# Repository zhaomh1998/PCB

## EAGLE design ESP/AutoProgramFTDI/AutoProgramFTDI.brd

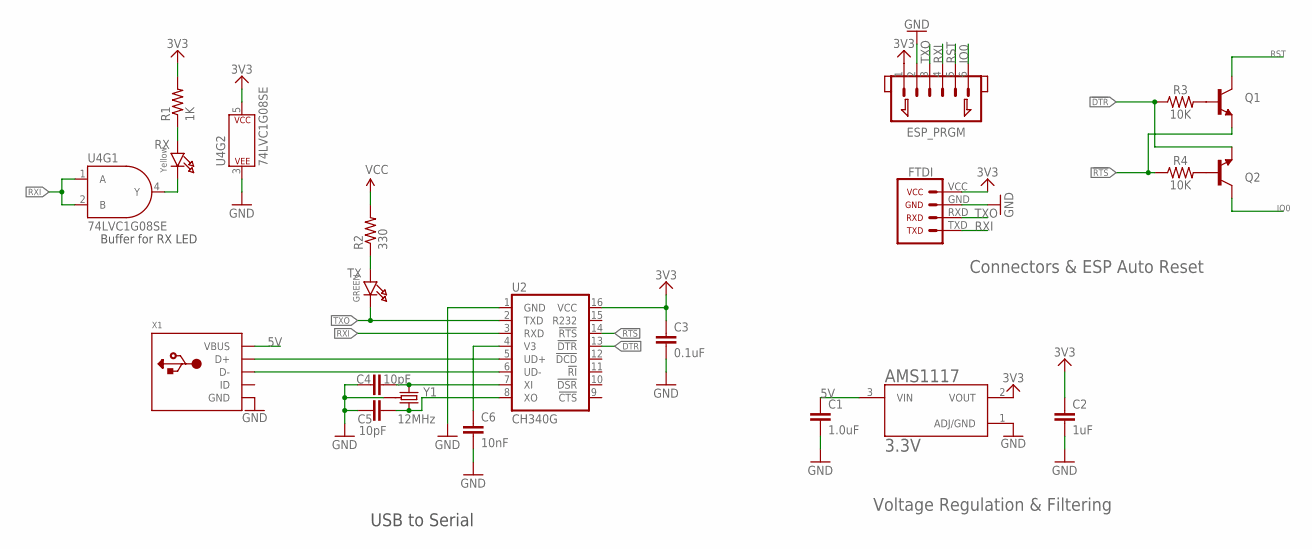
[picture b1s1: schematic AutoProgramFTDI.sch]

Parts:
AMS1117: 3.3V; SOT229P700X180-4N
C1: 1.0uF; 0603-CAP
C2: 1uF; 0603-CAP
C3: 0.1uF; 0603-CAP
C4, C5: 10pF; 0603-CAP
C6: 10nF; 0603-CAP
ESP_PRGM: JST_1.25_6P; JST1.25_6P
Q1, Q2: TRANSISTOR_NPNSOT23-3; SPARKFUN_SOT23-3
R1: 1K; 0603
R2: 330; 0603
R3, R4: 10K; 0603
RX: Yellow; MICROBUILDER_CHIPLED_0603
TX: GREEN; MICROBUILDER_CHIPLED_0603
U2: CH340G; SO016
U4: 74LVC1G08SE; SOT353
U$6: FTDI; 1X06
X1: USB_MICRO_20329_V2; MICROUSB_4UCONN_20329_V2
Y1: 12MHz; CRYSTAL-SMD-3.2X2.5

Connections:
3.3V: AMS1117.2 (VOUT), C2.1, C3.1, ESP_PRGM.1, R1.2, U2.16 (VCC), U4.5 (P$V+), U$6.VCC
5V: AMS1117.3 (VIN), C1.1, X1.VBUS
!DTR: Q2.2 (E), R3.1, U2.13 (!DTR)
!RTS: Q1.2 (E), R4.1, U2.14 (!RTS)
GND: AMS1117.1 (ADJ/GND), C1.2, C2.2, C3.2, C4.1, C5.1, C6.2, ESP_PRGM.2, U2.1 (GND), U4.3 (P$V-), U$6.GND, X1.BASE@1 (GND), X1.BASE@2 (GND), X1.GND, X1.SPRT@1 (GND), X1.SPRT@2 (GND), X1.SPRT@3 (GND), X1.SPRT@4 (GND), Y1.2 (GND), Y1.4 (GND)
IO0: ESP_PRGM.6, Q2.3 (C)
unnamed: R2.1, TX.A
unnamed: R1.1, RX.A
unnamed: C5.2, U2.8 (XO), Y1.3 (2)
unnamed: C4.2, U2.7 (XI), Y1.1
unnamed: RX.C, U4.4 (Y)
unnamed: U2.6 (UD-), X1.D-
unnamed: U2.5 (UD+), X1.D+
unnamed: Q1.1 (B), R3.2
unnamed: Q2.1 (B), R4.2
RST: ESP_PRGM.5, Q1.3 (C)
RXI: ESP_PRGM.4, U2.3 (RXD), U4.1 (A), U4.2 (B), U$6.TXD
TXO: ESP_PRGM.3, TX.C, U2.2 (TXD), U$6.RXD
V3: C6.1, U2.4 (V3)
VCC: R2.2

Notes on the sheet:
USB to Serial
Buffer for RX LED
Voltage Regulation & Filtering
Connectors & ESP Auto Reset

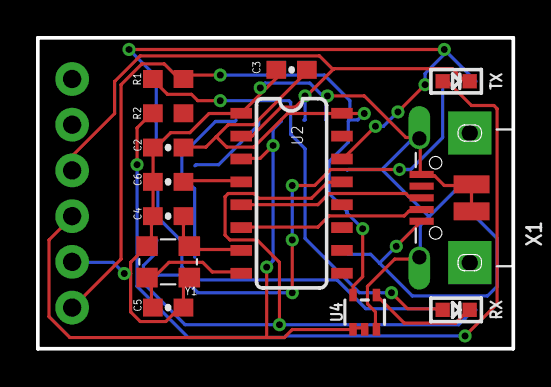
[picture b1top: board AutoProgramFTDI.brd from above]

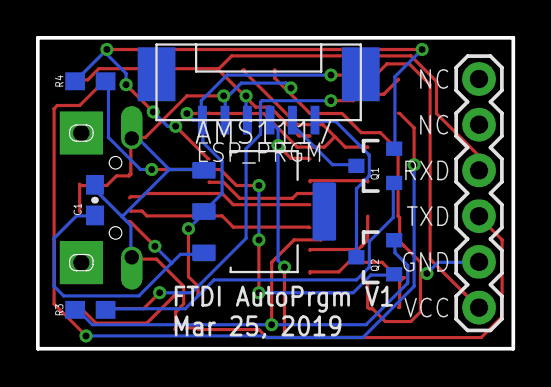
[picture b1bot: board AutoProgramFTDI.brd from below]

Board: 2 copper layers, 26.4 x 17.3 mm, 21 parts (8 on the bottom side), 19 nets.

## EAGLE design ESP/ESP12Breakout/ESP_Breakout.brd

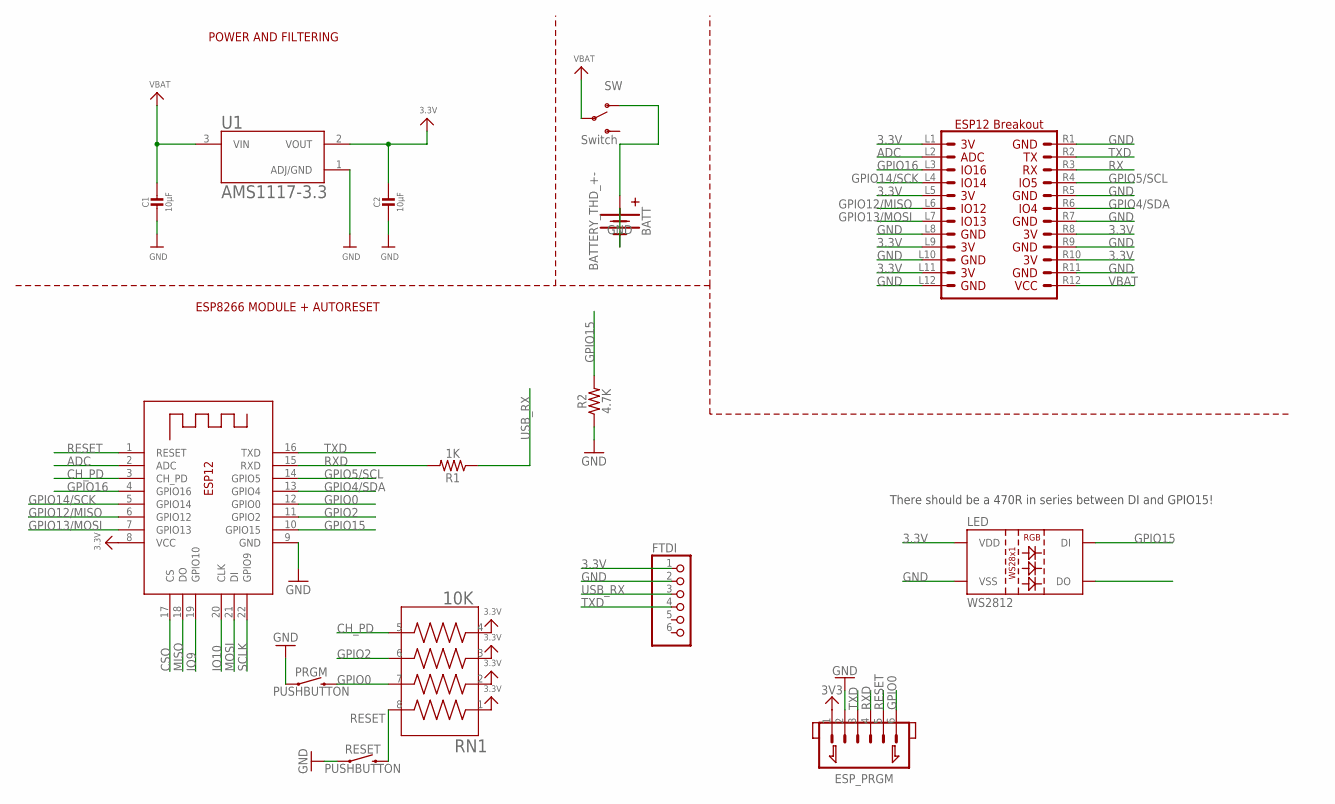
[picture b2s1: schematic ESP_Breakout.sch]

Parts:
BATT: BATTERY_THD_+-; 1X02_PLUS_MINUS
C1, C2: 10µF; CAP_0603
ESP_PRGM: JST_1.25_6P; JST1.25_6P
FTDI: PINHD-1X6; 1X06
LED: WS2812; LED-TRICOLOR-5050-IC
PRGM: PUSHBUTTON; TACTILE_SWITCH_SMD_6.0X3.5MM
R1: 1K; 0603
R2: 4.7K; 0603
RESET: PUSHBUTTON; TACTILE_SWITCH_SMD_6.0X3.5MM
RN1: 10K; RESCAF80P320X160X60-8N
SW: Switch; SWITCH_SPDT_PTH_11.6X4.0MM
U1: AMS1117-3.3; SOT229P700X180-4N
U$7: ESP12_BREAKOUT; ESP12_BREAKOUT_CONN
X2: ESP-12; ESP-12E

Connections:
3.3V: C2.1, ESP_PRGM.1, FTDI.1, LED.VDD, RN1.1, RN1.2, RN1.3, RN1.4, U1.2 (VOUT), U$7.L1, U$7.L5, U$7.L9, U$7.L11, U$7.R8, U$7.R10, X2.8 (VCC)
ADC: U$7.L2, X2.2 (ADC)
CH_PD: RN1.5, X2.3 (CH_PD)
CSO: X2.17 (CS)
GND: BATT.-, C1.2, C2.2, ESP_PRGM.2, FTDI.2, LED.VSS, PRGM.1, R2.1, RESET.1, U1.1 (ADJ/GND), U$7.L8, U$7.L10, U$7.L12, U$7.R1, U$7.R5, U$7.R7, U$7.R9, U$7.R11, X2.9 (GND)
GPIO0: ESP_PRGM.6, PRGM.2, RN1.7, X2.12 (GPIO0)
GPIO2: RN1.6, X2.11 (GPIO2)
GPIO4/SDA: U$7.R6, X2.13 (GPIO4)
GPIO5/SCL: U$7.R4, X2.14 (GPIO5)
GPIO12/MISO: U$7.L6, X2.6 (GPIO12)
GPIO13/MOSI: U$7.L7, X2.7 (GPIO13)
GPIO14/SCK: U$7.L4, X2.5 (GPIO14)
GPIO15: LED.DIN (DI), R2.2, X2.10 (GPIO15)
GPIO16: U$7.L3, X2.4 (GPIO16)
IO9: X2.19 (GPIO10)
IO10: X2.20 (CLK)
MISO: X2.18 (DO)
MOSI: X2.21 (DI)
unnamed: BATT.+, SW.1 (O)
RESET: ESP_PRGM.5, RESET.2, RN1.8, X2.1 (RESET)
RX: U$7.R3
RXD: ESP_PRGM.4, R1.2, X2.15 (RXD)
SCLK: X2.22 (GPIO9)
TXD: ESP_PRGM.3, FTDI.4, U$7.R2, X2.16 (TXD)
USB_RX: FTDI.3, R1.1
VBAT: C1.1, SW.2, U1.3 (VIN), U$7.R12

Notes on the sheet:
POWER AND FILTERING
ESP8266 MODULE + AUTORESET
There should be a 470R in series between DI and GPIO15!

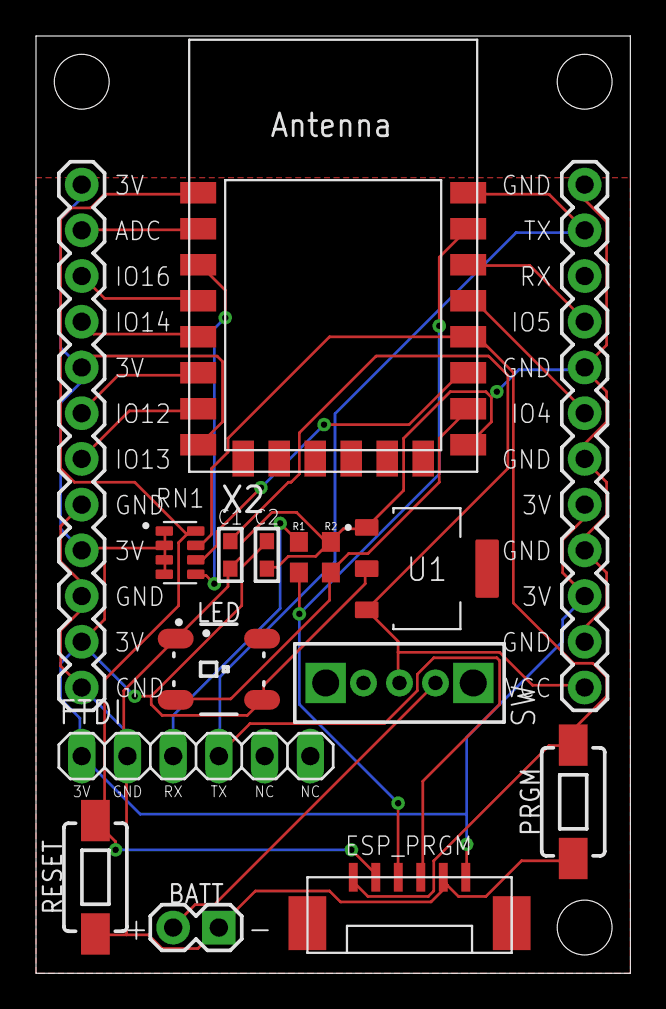
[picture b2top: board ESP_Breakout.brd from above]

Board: 2 copper layers, 33.0 x 52.1 mm, 15 parts (0 on the bottom side), 19 nets.

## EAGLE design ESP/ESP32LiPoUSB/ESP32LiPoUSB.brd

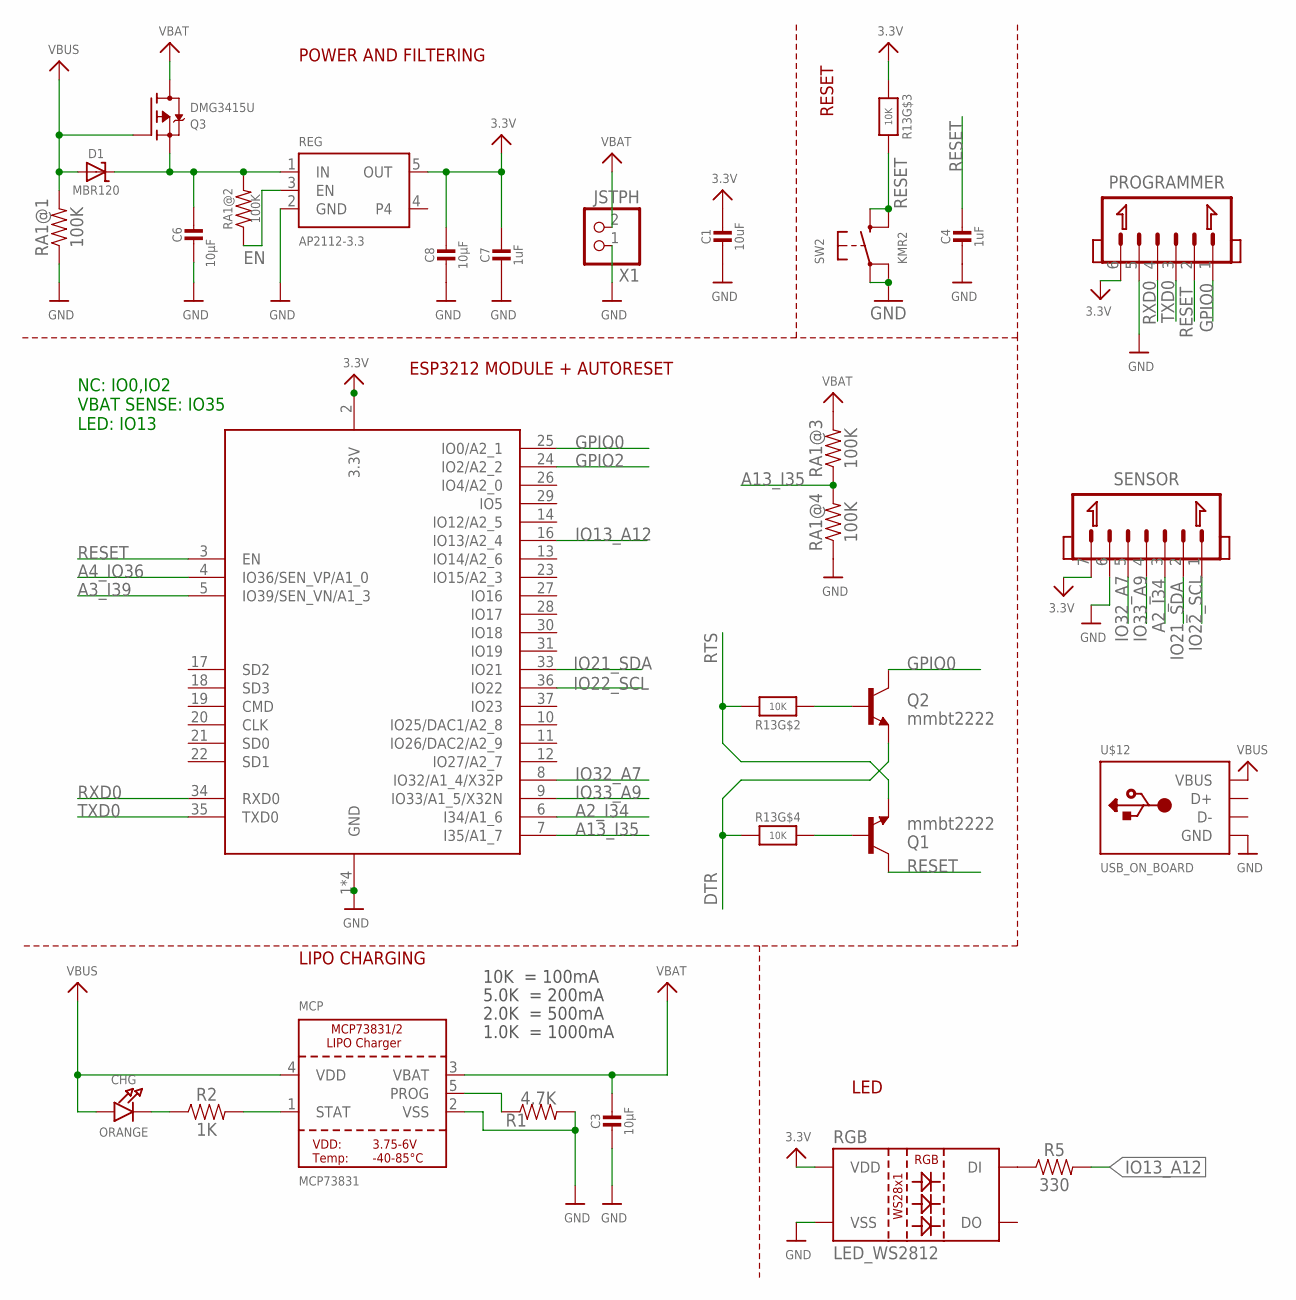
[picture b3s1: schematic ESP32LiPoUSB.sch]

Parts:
C1: 10uF; CAP_0805
C3, C8: 10µF; CAP_0805
C4, C7: 1uF; CAP_0603
C6: 10µF; CAP_0603
CHG: ORANGE; MICROBUILDER_CHIPLED_0603
D1: MBR120; SOD-123
MCP: MCP73831; SOT23-5
PROGRAMMER: JST_1.25_6P; JST1.25_6P
Q1, Q2: mmbt2222; SOT23-3
Q3: DMG3415U; SOT23-R
R1: 4.7K; 0603
R2: 1K; 0603
R5: 330; 0603
R13: 10K; RESPACK_4X0603
RA1: 100K; RESCAF80P320X160X60-8N
REG: AP2112-3.3; SOT23-5
RGB: LED_WS2812; LED-TRICOLOR-5050-IC
SENSOR: JST_1.25_7P; JST1.25_7P
SW2: KMR2; BTN_KMR2_4.6X2.8
U$12: USB_ON_BOARD
X1: JSTPH; JSTPH2
X2: ESP32_WROOM32_SKINNY; WROOM32_SKINNY

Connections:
3.3V: C1.1, C7.1, C8.1, PROGRAMMER.6, R13.3 (1), REG.5 (OUT), RGB.VDD, SENSOR.7, X2.2 (3.3V)
A2_I34: SENSOR.3, X2.6 (I34/A1_6)
A3_I39: X2.5 (IO39/SEN_VN/A1_3)
A4_IO36: X2.4 (IO36/SEN_VP/A1_0)
A13_I35: RA1.3 (1), RA1.8 (2), X2.7 (I35/A1_7)
DTR: Q2.2 (E), R13.4 (1)
EN: RA1.2 (1), REG.3 (EN)
GND: C1.2, C3.2, C4.2, C6.2, C7.2, C8.2, MCP.2 (VSS), PROGRAMMER.5, R1.2, RA1.1, RA1.4 (1), REG.2 (GND), RGB.VSS, SENSOR.6, SW2.A, SW2.A' (P1), U$12.GND, X1.1, X2.1 (GND), X2.15 (GND), X2.38 (GND), X2.P$1 (GND)
GPIO0: PROGRAMMER.1, Q2.3 (C), X2.25 (IO0/A2_1)
GPIO2: X2.24 (IO2/A2_2)
IO13_A12: R5.2, X2.16 (IO13/A2_4)
IO21_SDA: SENSOR.2, X2.33 (IO21)
IO22_SCL: SENSOR.1, X2.36 (IO22)
IO32_A7: SENSOR.5, X2.8 (IO32/A1_4/X32P)
IO33_A9: SENSOR.4, X2.9 (IO33/A1_5/X32N)
unnamed: CHG.C, R2.1
unnamed: R5.1, RGB.DIN (DI)
unnamed: MCP.1 (STAT), R2.2
unnamed: MCP.5 (PROG), R1.1
unnamed: C6.1, D1.C, Q3.2 (S), RA1.6 (2), REG.1 (IN)
unnamed: Q1.1 (B), R13.5 (2)
unnamed: Q2.1 (B), R13.2 (1)
RESET: C4.1, PROGRAMMER.2, Q1.3 (C), R13.6 (2), SW2.B (S), SW2.B' (S1), X2.3 (EN)
RTS: Q1.2 (E), R13.7 (2)
RXD0: PROGRAMMER.4, X2.34 (RXD0)
TXD0: PROGRAMMER.3, X2.35 (TXD0)
VBAT: C3.1, MCP.3 (VBAT), Q3.3 (D), RA1.7 (2), X1.2
VBUS: CHG.A, D1.A, MCP.4 (VDD), Q3.1 (G), RA1.5 (2), U$12.VCC (VBUS)

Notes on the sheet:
POWER AND FILTERING
RESET
10K = 100mA
5.0K = 200mA
2.0K = 500mA
1.0K = 1000mA
LIPO CHARGING
LED
ESP3212 MODULE + AUTORESET
NC: IO0,IO2 VBAT SENSE: IO35 LED: IO13

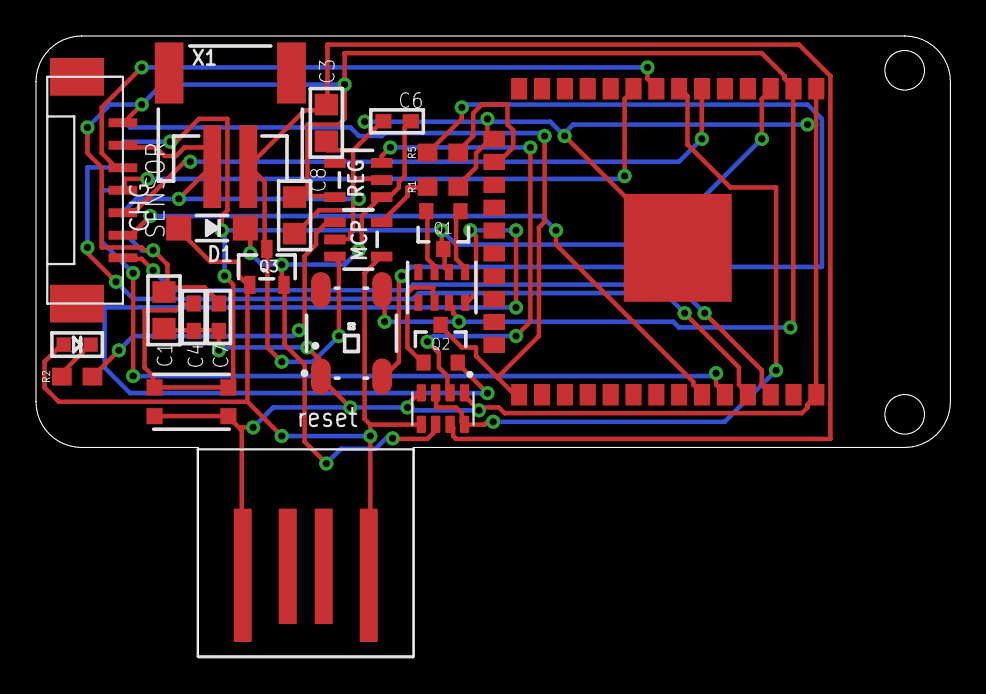
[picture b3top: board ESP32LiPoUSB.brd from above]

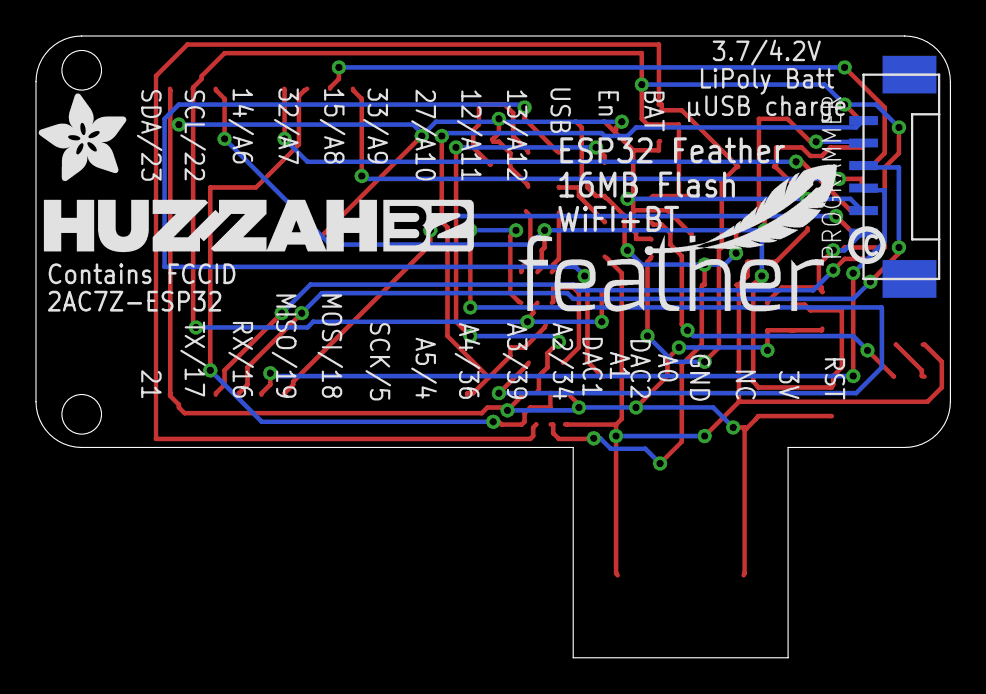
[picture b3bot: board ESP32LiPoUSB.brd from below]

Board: 2 copper layers, 50.8 x 34.5 mm, 29 parts (5 on the bottom side), 25 nets.

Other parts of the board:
U$7: ADAFRUIT_5MM
U$9: FEATHERLOGO_MED
U$13: PCBFEAT-REV-040
U$43: HUZZAH32

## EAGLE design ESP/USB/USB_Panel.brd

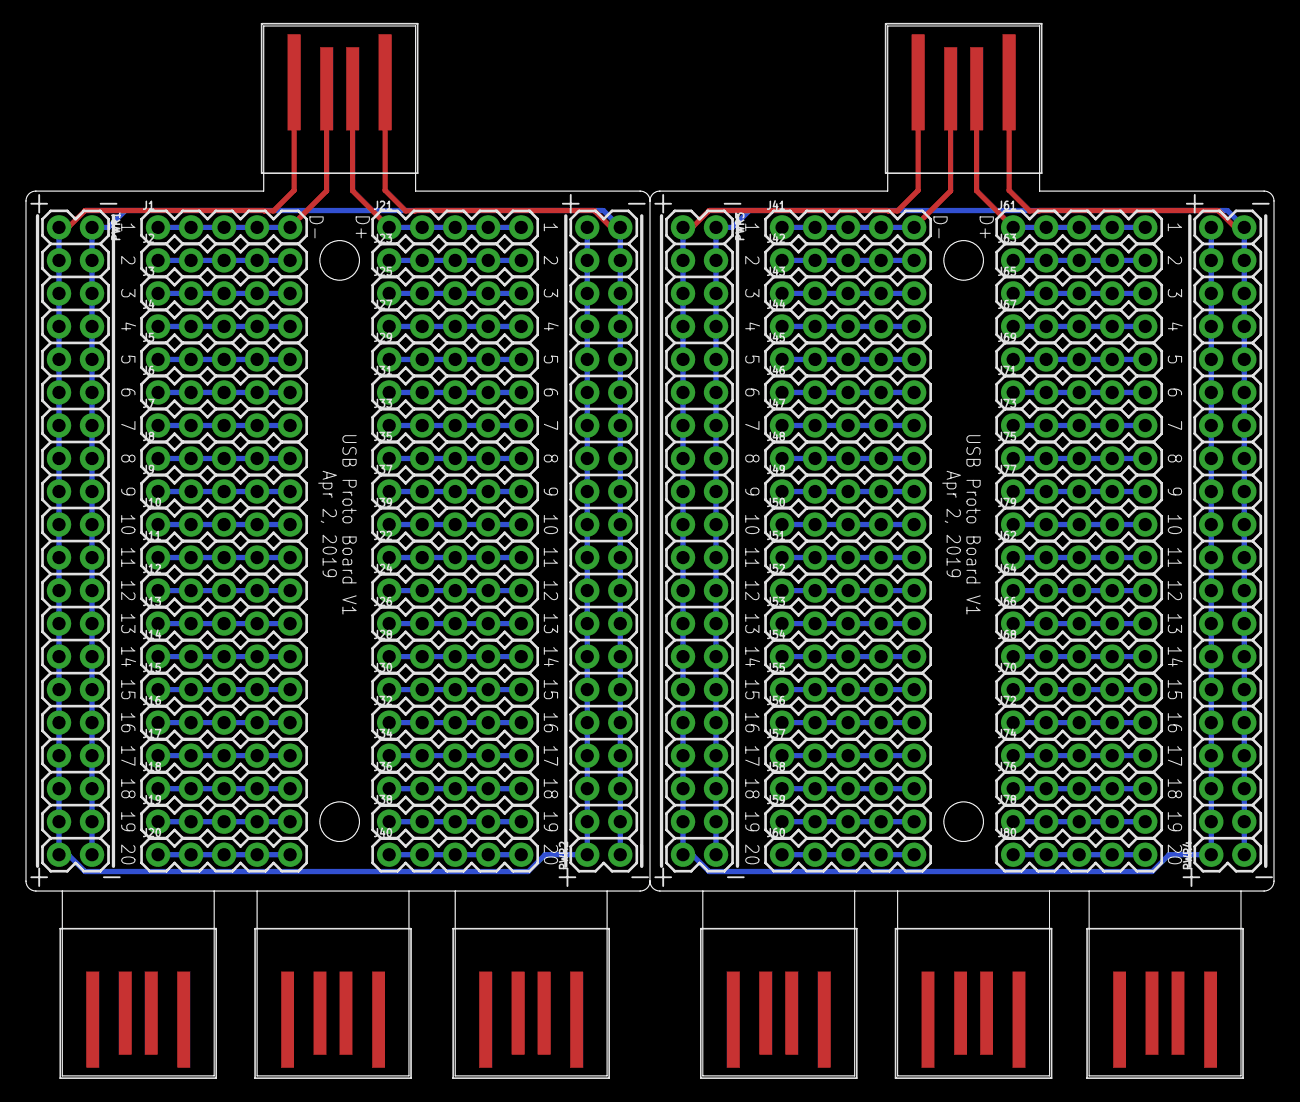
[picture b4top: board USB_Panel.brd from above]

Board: 2 copper layers, 96.0 x 66.5 mm, 92 parts (0 on the bottom side), 84 nets.

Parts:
J1, J2, J3, J4, J5, J6, J7, J8, J9, J10, J11, J12, J13, J14, J15, J16, J17, J18, J19, J20, J21, J22, J23, J24, J25, J26, J27, J28, J29, J30, J31, J32, J33, J34, J35, J36, J37, J38, J39, J40, J41, J42, J43, J44, J45, J46, J47, J48, J49, J50, J51, J52, J53, J54, J55, J56, J57, J58, J59, J60, J61, J62, J63, J64, J65, J66, J67, J68, J69, J70, J71, J72, J73, J74, J75, J76, J77, J78, J79, J80: 1X05
PWR1, PWR2, PWR3, PWR4: CONN_20X2; 2X20
U$1, U$2, U$3, U$4, U$5, U$6, U$7, U$8: USB_ON_BOARD

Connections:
unnamed: J1.1, J1.2, J1.3, J1.4, J1.5, U$2.D-
unnamed: J2.1, J2.2, J2.3, J2.4, J2.5
unnamed: J3.1, J3.2, J3.3, J3.4, J3.5
unnamed: J4.1, J4.2, J4.3, J4.4, J4.5
unnamed: J5.1, J5.2, J5.3, J5.4, J5.5
unnamed: J6.1, J6.2, J6.3, J6.4, J6.5
unnamed: J7.1, J7.2, J7.3, J7.4, J7.5
unnamed: J8.1, J8.2, J8.3, J8.4, J8.5
unnamed: J9.1, J9.2, J9.3, J9.4, J9.5
unnamed: J10.1, J10.2, J10.3, J10.4, J10.5
unnamed: J11.1, J11.2, J11.3, J11.4, J11.5
unnamed: J12.1, J12.2, J12.3, J12.4, J12.5
unnamed: J13.1, J13.2, J13.3, J13.4, J13.5
unnamed: J14.1, J14.2, J14.3, J14.4, J14.5
unnamed: J15.1, J15.2, J15.3, J15.4, J15.5
unnamed: J16.1, J16.2, J16.3, J16.4, J16.5
unnamed: J17.1, J17.2, J17.3, J17.4, J17.5
unnamed: J18.1, J18.2, J18.3, J18.4, J18.5
unnamed: J19.1, J19.2, J19.3, J19.4, J19.5
unnamed: J20.1, J20.2, J20.3, J20.4, J20.5
unnamed: J21.1, J21.2, J21.3, J21.4, J21.5, U$2.D+
unnamed: J22.1, J22.2, J22.3, J22.4, J22.5
unnamed: J23.1, J23.2, J23.3, J23.4, J23.5
unnamed: J24.1, J24.2, J24.3, J24.4, J24.5
unnamed: J25.1, J25.2, J25.3, J25.4, J25.5
unnamed: J26.1, J26.2, J26.3, J26.4, J26.5
unnamed: J27.1, J27.2, J27.3, J27.4, J27.5
unnamed: J28.1, J28.2, J28.3, J28.4, J28.5
unnamed: J29.1, J29.2, J29.3, J29.4, J29.5
unnamed: J30.1, J30.2, J30.3, J30.4, J30.5
unnamed: J31.1, J31.2, J31.3, J31.4, J31.5
unnamed: J32.1, J32.2, J32.3, J32.4, J32.5
unnamed: J33.1, J33.2, J33.3, J33.4, J33.5
unnamed: J34.1, J34.2, J34.3, J34.4, J34.5
unnamed: J35.1, J35.2, J35.3, J35.4, J35.5
unnamed: J36.1, J36.2, J36.3, J36.4, J36.5
unnamed: J37.1, J37.2, J37.3, J37.4, J37.5
unnamed: J38.1, J38.2, J38.3, J38.4, J38.5
unnamed: J39.1, J39.2, J39.3, J39.4, J39.5
unnamed: J40.1, J40.2, J40.3, J40.4, J40.5
unnamed: PWR1.1, PWR1.3, PWR1.5, PWR1.7, PWR1.9, PWR1.11, PWR1.13, PWR1.15, PWR1.17, PWR1.19, PWR1.21, PWR1.23, PWR1.25, PWR1.27, PWR1.29, PWR1.31, PWR1.33, PWR1.35, PWR1.37, PWR1.39, PWR2.2, PWR2.4, PWR2.6, PWR2.8, PWR2.10, PWR2.12, PWR2.14, PWR2.16, PWR2.18, PWR2.20, PWR2.22, PWR2.24, PWR2.26, PWR2.28, PWR2.30, PWR2.32, PWR2.34, PWR2.36, PWR2.38, PWR2.40, U$2.VCC
unnamed: PWR1.2, PWR1.4, PWR1.6, PWR1.8, PWR1.10, PWR1.12, PWR1.14, PWR1.16, PWR1.18, PWR1.20, PWR1.22, PWR1.24, PWR1.26, PWR1.28, PWR1.30, PWR1.32, PWR1.34, PWR1.36, PWR1.38, PWR1.40, PWR2.1, PWR2.3, PWR2.5, PWR2.7, PWR2.9, PWR2.11, PWR2.13, PWR2.15, PWR2.17, PWR2.19, PWR2.21, PWR2.23, PWR2.25, PWR2.27, PWR2.29, PWR2.31, PWR2.33, PWR2.35, PWR2.37, PWR2.39, U$2.GND
unnamed: J41.1, J41.2, J41.3, J41.4, J41.5, U$1.D-
unnamed: J42.1, J42.2, J42.3, J42.4, J42.5
unnamed: J43.1, J43.2, J43.3, J43.4, J43.5
unnamed: J44.1, J44.2, J44.3, J44.4, J44.5
unnamed: J45.1, J45.2, J45.3, J45.4, J45.5
unnamed: J46.1, J46.2, J46.3, J46.4, J46.5
unnamed: J47.1, J47.2, J47.3, J47.4, J47.5
unnamed: J48.1, J48.2, J48.3, J48.4, J48.5
unnamed: J49.1, J49.2, J49.3, J49.4, J49.5
unnamed: J50.1, J50.2, J50.3, J50.4, J50.5
unnamed: J51.1, J51.2, J51.3, J51.4, J51.5
unnamed: J52.1, J52.2, J52.3, J52.4, J52.5
unnamed: J53.1, J53.2, J53.3, J53.4, J53.5
unnamed: J54.1, J54.2, J54.3, J54.4, J54.5
unnamed: J55.1, J55.2, J55.3, J55.4, J55.5
unnamed: J56.1, J56.2, J56.3, J56.4, J56.5
unnamed: J57.1, J57.2, J57.3, J57.4, J57.5
unnamed: J58.1, J58.2, J58.3, J58.4, J58.5
unnamed: J59.1, J59.2, J59.3, J59.4, J59.5
unnamed: J60.1, J60.2, J60.3, J60.4, J60.5
unnamed: J61.1, J61.2, J61.3, J61.4, J61.5, U$1.D+
unnamed: J62.1, J62.2, J62.3, J62.4, J62.5
unnamed: J63.1, J63.2, J63.3, J63.4, J63.5
unnamed: J64.1, J64.2, J64.3, J64.4, J64.5
unnamed: J65.1, J65.2, J65.3, J65.4, J65.5
unnamed: J66.1, J66.2, J66.3, J66.4, J66.5
unnamed: J67.1, J67.2, J67.3, J67.4, J67.5
unnamed: J68.1, J68.2, J68.3, J68.4, J68.5
unnamed: J69.1, J69.2, J69.3, J69.4, J69.5
unnamed: J70.1, J70.2, J70.3, J70.4, J70.5
unnamed: J71.1, J71.2, J71.3, J71.4, J71.5
unnamed: J72.1, J72.2, J72.3, J72.4, J72.5
unnamed: J73.1, J73.2, J73.3, J73.4, J73.5
unnamed: J74.1, J74.2, J74.3, J74.4, J74.5
unnamed: J75.1, J75.2, J75.3, J75.4, J75.5
unnamed: J76.1, J76.2, J76.3, J76.4, J76.5
unnamed: J77.1, J77.2, J77.3, J77.4, J77.5
unnamed: J78.1, J78.2, J78.3, J78.4, J78.5
unnamed: J79.1, J79.2, J79.3, J79.4, J79.5
unnamed: J80.1, J80.2, J80.3, J80.4, J80.5
unnamed: PWR3.1, PWR3.3, PWR3.5, PWR3.7, PWR3.9, PWR3.11, PWR3.13, PWR3.15, PWR3.17, PWR3.19, PWR3.21, PWR3.23, PWR3.25, PWR3.27, PWR3.29, PWR3.31, PWR3.33, PWR3.35, PWR3.37, PWR3.39, PWR4.2, PWR4.4, PWR4.6, PWR4.8, PWR4.10, PWR4.12, PWR4.14, PWR4.16, PWR4.18, PWR4.20, PWR4.22, PWR4.24, PWR4.26, PWR4.28, PWR4.30, PWR4.32, PWR4.34, PWR4.36, PWR4.38, PWR4.40, U$1.VCC
unnamed: PWR3.2, PWR3.4, PWR3.6, PWR3.8, PWR3.10, PWR3.12, PWR3.14, PWR3.16, PWR3.18, PWR3.20, PWR3.22, PWR3.24, PWR3.26, PWR3.28, PWR3.30, PWR3.32, PWR3.34, PWR3.36, PWR3.38, PWR3.40, PWR4.1, PWR4.3, PWR4.5, PWR4.7, PWR4.9, PWR4.11, PWR4.13, PWR4.15, PWR4.17, PWR4.19, PWR4.21, PWR4.23, PWR4.25, PWR4.27, PWR4.29, PWR4.31, PWR4.33, PWR4.35, PWR4.37, PWR4.39, U$1.GND

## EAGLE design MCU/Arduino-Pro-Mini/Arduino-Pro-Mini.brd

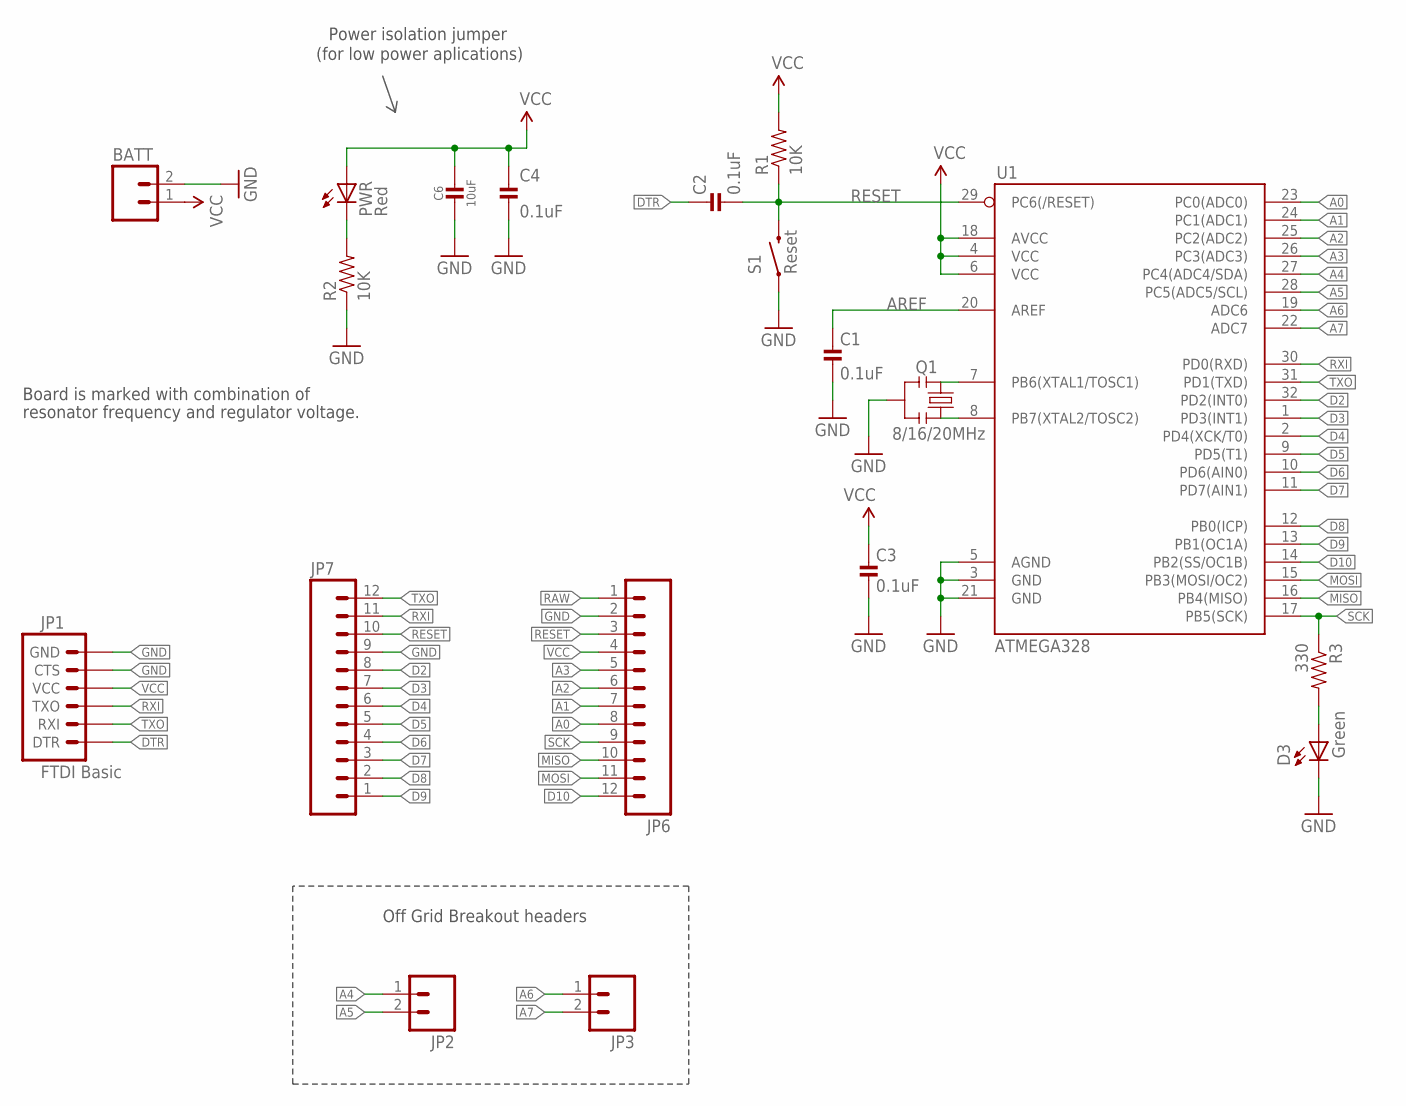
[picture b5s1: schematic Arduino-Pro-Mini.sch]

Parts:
BATT: M02PTH; 1X02
C1, C2, C3, C4: 0.1uF; CAP_0603
C6: 10uF; CAP_0805
D3: Green; 0603-LED-ALT1
JP1: FTDI Basic; 1X06
JP2, JP3: M02PTH; 1X02
JP6, JP7: M12PTH; 1X12
PWR: Red; 0603-LED-ALT1
Q1: 8/16/20MHz; RESONATOR-SMD-1:1
R1, R2: 10K; 0603
R3: 330; 0603
S1: Reset; TACTILE_SWITCH_SMD_6.0X3.5MM
U1: ATMEGA328; TQFP32-08

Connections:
3.3V: BATT.1
A0: JP6.8, U1.23 (PC0(ADC0))
A1: JP6.7, U1.24 (PC1(ADC1))
A2: JP6.6, U1.25 (PC2(ADC2))
A3: JP6.5, U1.26 (PC3(ADC3))
A4: JP2.1, U1.27 (PC4(ADC4/SDA))
A5: JP2.2, U1.28 (PC5(ADC5/SCL))
A6: JP3.1, U1.19 (ADC6)
A7: JP3.2, U1.22 (ADC7)
AREF: C1.2, U1.20 (AREF)
D2: JP7.8, U1.32 (PD2(INT0))
D3: JP7.7, U1.1 (PD3(INT1))
D4: JP7.6, U1.2 (PD4(XCK/T0))
D5: JP7.5, U1.9 (PD5(T1))
D6: JP7.4, U1.10 (PD6(AIN0))
D7: JP7.3, U1.11 (PD7(AIN1))
D8: JP7.2, U1.12 (PB0(ICP))
D9: JP7.1, U1.13 (PB1(OC1A))
D10: JP6.12, U1.14 (PB2(SS/OC1B))
DTR: C2.2, JP1.1 (DTR)
GND: BATT.2, C1.1, C3.1, C4.2, C6.2, D3.C, JP1.5 (CTS), JP1.6 (GND), JP6.2, JP7.9, Q1.2, R2.1, S1.1, U1.3 (GND), U1.5 (AGND), U1.21 (GND)
MISO: JP6.10, U1.16 (PB4(MISO))
MOSI: JP6.11, U1.15 (PB3(MOSI/OC2))
unnamed: Q1.3, U1.8 (PB7(XTAL2/TOSC2))
unnamed: Q1.1, U1.7 (PB6(XTAL1/TOSC1))
unnamed: PWR.C, R2.2
unnamed: D3.A, R3.2
RAW: JP6.1
RESET: C2.1, JP6.3, JP7.10, R1.1, S1.2, U1.29 (PC6(/RESET))
RXI: JP1.3 (TXO), JP7.11, U1.30 (PD0(RXD))
SCK: JP6.9, R3.1, U1.17 (PB5(SCK))
TXO: JP1.2 (RXI), JP7.12, U1.31 (PD1(TXD))
VCC: C3.2, C4.1, C6.1, JP1.4 (VCC), JP6.4, PWR.A, R1.2, U1.4 (VCC), U1.6 (VCC), U1.18 (AVCC)

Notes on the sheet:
Board is marked with combination of
resonator frequency and regulator voltage.
Off Grid Breakout headers
Power isolation jumper
(for low power aplications)

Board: 2 copper layers, 19 parts (5 on the bottom side), 31 nets, no tracks yet.

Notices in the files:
parts and their libraries:
SparkFun-Capacitors: Licensing: Creative Commons ShareAlike 4.0 International - https://creativecommons.org/licenses/by-sa/4.0
SparkFun-Aesthetics: Licensing: CC v3.0 Share-Alike You are welcome to use this library for commercial purposes.
